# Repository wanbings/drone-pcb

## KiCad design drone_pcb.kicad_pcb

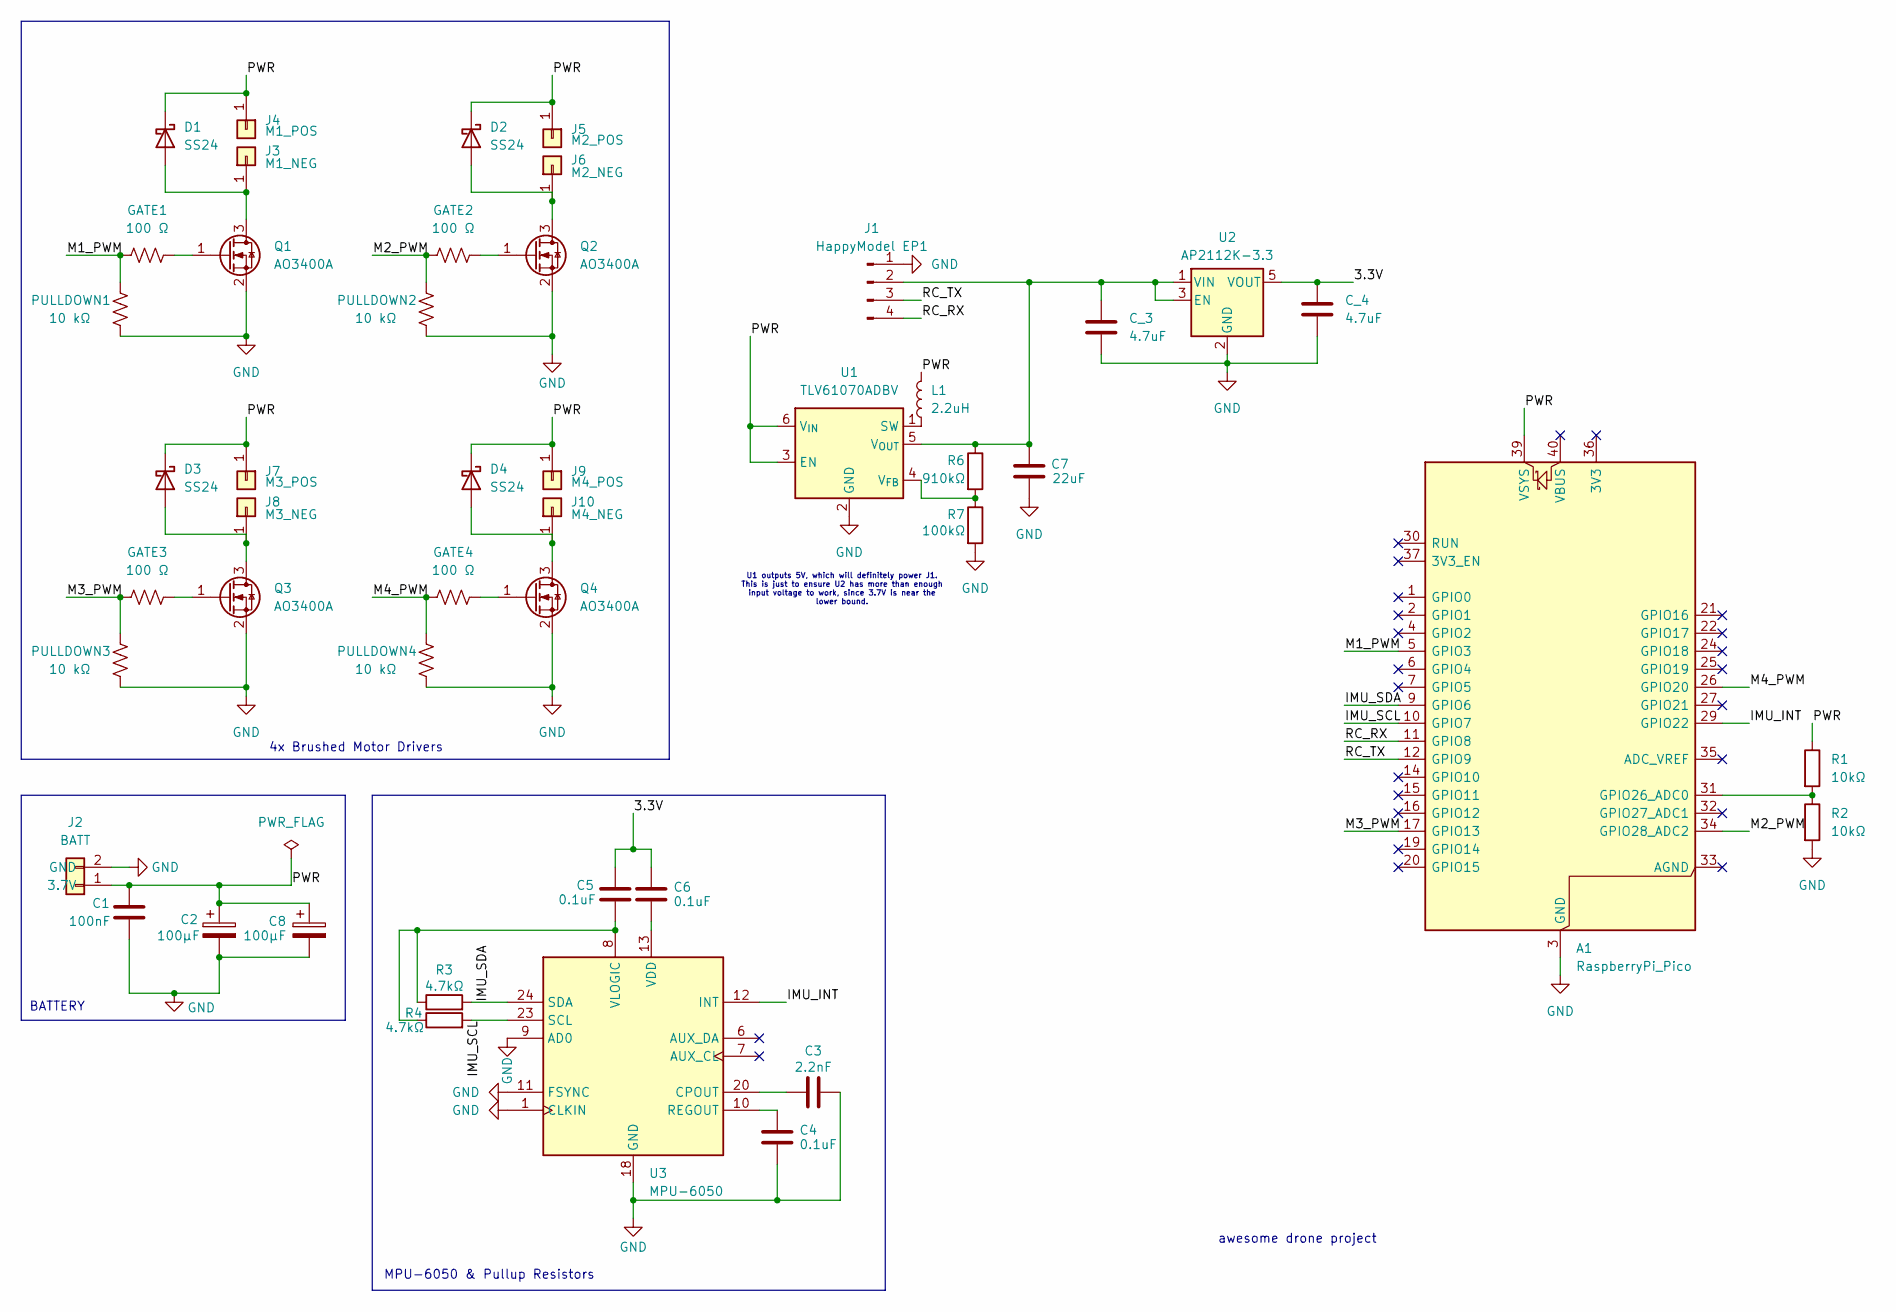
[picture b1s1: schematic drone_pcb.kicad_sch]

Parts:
A1: RaspberryPi_Pico; RaspberryPi_Pico_Common_Unspecified
C1: 100nF; C_0805_2012Metric
C2, C8: 100µF; C_1206_3216Metric
C3: 2.2nF; C_0805_2012Metric
C4, C5, C6: 0.1uF; C_0805_2012Metric
C7: 22uF; C_0805_2012Metric
C_3, C_4: 4.7uF; C_0805_2012Metric
D1, D2, D3, D4: SS24; D_SMA
GATE1, GATE2, GATE3, GATE4: 100 Ω; R_0805_2012Metric
J1: HappyModel EP1; PinHeader_1x04_P2.54mm_Vertical
J2: BATT; JST_PH_S2B-PH-K_1x02_P2.00mm_Horizontal
J3: M1_NEG; SolderWire-0.25sqmm_1x01_D0.65mm_OD1.7mm
J4: M1_POS; SolderWire-0.25sqmm_1x01_D0.65mm_OD1.7mm
J5: M2_POS; SolderWire-0.25sqmm_1x01_D0.65mm_OD1.7mm
J6: M2_NEG; SolderWire-0.25sqmm_1x01_D0.65mm_OD1.7mm
J7: M3_POS; SolderWire-0.25sqmm_1x01_D0.65mm_OD1.7mm
J8: M3_NEG; SolderWire-0.25sqmm_1x01_D0.65mm_OD1.7mm
J9: M4_POS; SolderWire-0.25sqmm_1x01_D0.65mm_OD1.7mm
J10: M4_NEG; SolderWire-0.25sqmm_1x01_D0.65mm_OD1.7mm
L1: 2.2uH; L_1008_2520Metric
PULLDOWN1, PULLDOWN2, PULLDOWN3, PULLDOWN4: 10 kΩ; R_0805_2012Metric
Q1, Q2, Q3, Q4: AO3400A; SOT-23
R1, R2: 10kΩ; R_0805_2012Metric
R3, R4: 4.7kΩ; R_0805_2012Metric
R6: 910kΩ; R_0805_2012Metric
R7: 100kΩ; R_0805_2012Metric
U1: TLV61070ADBV; SOT-23-6
U2: AP2112K-3.3; SOT-23-5
U3: MPU-6050; InvenSense_QFN-24_4x4mm_P0.5mm

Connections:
/3.3V: C5.1, C6.1, C_4.1, U2.5 (VOUT)
/IMU_INT: A1.29 (GPIO22), U3.12 (INT)
/IMU_SCL: A1.10 (GPIO7), R4.2, U3.23 (SCL)
/IMU_SDA: A1.9 (GPIO6), R3.2, U3.24 (SDA)
/M1_PWM: A1.5 (GPIO3), GATE1.1, PULLDOWN1.2
/M2_PWM: A1.34 (GPIO28_ADC2), GATE2.1, PULLDOWN2.2
/M3_PWM: A1.17 (GPIO13), GATE3.1, PULLDOWN3.2
/M4_PWM: A1.26 (GPIO20), GATE4.1, PULLDOWN4.2
/PWR: A1.39 (VSYS), C1.1, C2.1, C8.1, D1.1 (K), D2.1 (K), D3.1 (K), D4.1 (K), J2.1 (3.7V), J4.1 (Pin_1_1), J5.1 (Pin_1_1), J7.1 (Pin_1_1), J9.1 (Pin_1_1), L1.2, R1.1, U1.3 (EN), U1.6 (V_{IN})
/RC_RX: A1.11 (GPIO8), J1.4
/RC_TX: A1.12 (GPIO9), J1.3
GND: A1.3 (GND), A1.8 (GND), A1.13 (GND), A1.18 (GND), A1.23 (GND), A1.28 (GND), A1.38 (GND), C1.2, C2.2, C3.2, C4.2, C7.2, C8.2, C_3.2, C_4.2, J1.1, J2.2 (GND), PULLDOWN1.1, PULLDOWN2.1, PULLDOWN3.1, PULLDOWN4.1, Q1.2 (S), Q2.2 (S), Q3.2 (S), Q4.2 (S), R2.2, R7.2, U1.2 (GND), U2.2 (GND), U3.1 (CLKIN), U3.9 (AD0), U3.11 (FSYNC), U3.18 (GND)
unnamed: A1.31 (GPIO26_ADC0), R1.2, R2.1
unnamed: D1.2 (A), J3.1 (Pin_1_1), Q1.3 (D)
unnamed: D2.2 (A), J6.1 (Pin_1_1), Q2.3 (D)
unnamed: D3.2 (A), J8.1 (Pin_1_1), Q3.3 (D)
unnamed: D4.2 (A), J10.1 (Pin_1_1), Q4.3 (D)
unnamed: C7.1, C_3.1, J1.2, R6.1, U1.5 (V_{OUT}), U2.1 (VIN), U2.3 (EN)
unnamed: GATE1.2, Q1.1 (G)
unnamed: GATE2.2, Q2.1 (G)
unnamed: GATE3.2, Q3.1 (G)
unnamed: GATE4.2, Q4.1 (G)
unnamed: L1.1, U1.1 (SW)
unnamed: R6.2, R7.1, U1.4 (V_{FB})
unnamed: C3.1, U3.20 (CPOUT)
unnamed: C4.1, U3.10 (REGOUT)
unnamed: C6.2, U3.13 (VDD)
unnamed: C5.2, R3.1, R4.1, U3.8 (VLOGIC)

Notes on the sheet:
MPU-6050 & Pullup Resistors
4x Brushed Motor Drivers
BATTERY
U1 outputs 5V, which will definitely power J1. This is just to ensure U2 has more than enough input voltage to work, since 3.7V is near the lower bound.
awesome drone project

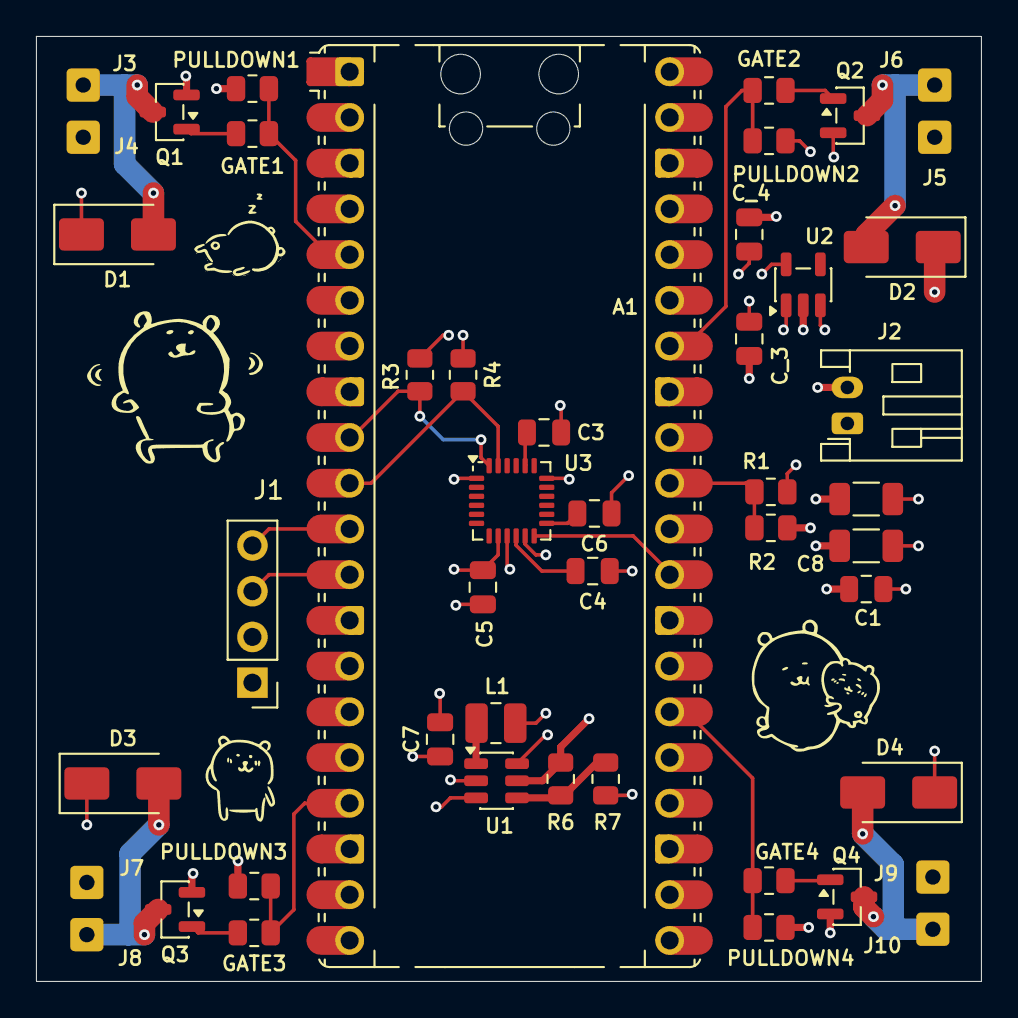
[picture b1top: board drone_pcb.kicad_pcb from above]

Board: 4 copper layers, 52.5 x 52.5 mm, 47 parts (0 on the bottom side), 28 nets.

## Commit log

2026-05-24 first commit ayyy
2026-05-26 schematic done now i think???
2026-05-29 in the middle of adding traces
2026-05-30 first draft (not usable)
2026-06-01 final draft i think
2026-06-02 actual final draft
